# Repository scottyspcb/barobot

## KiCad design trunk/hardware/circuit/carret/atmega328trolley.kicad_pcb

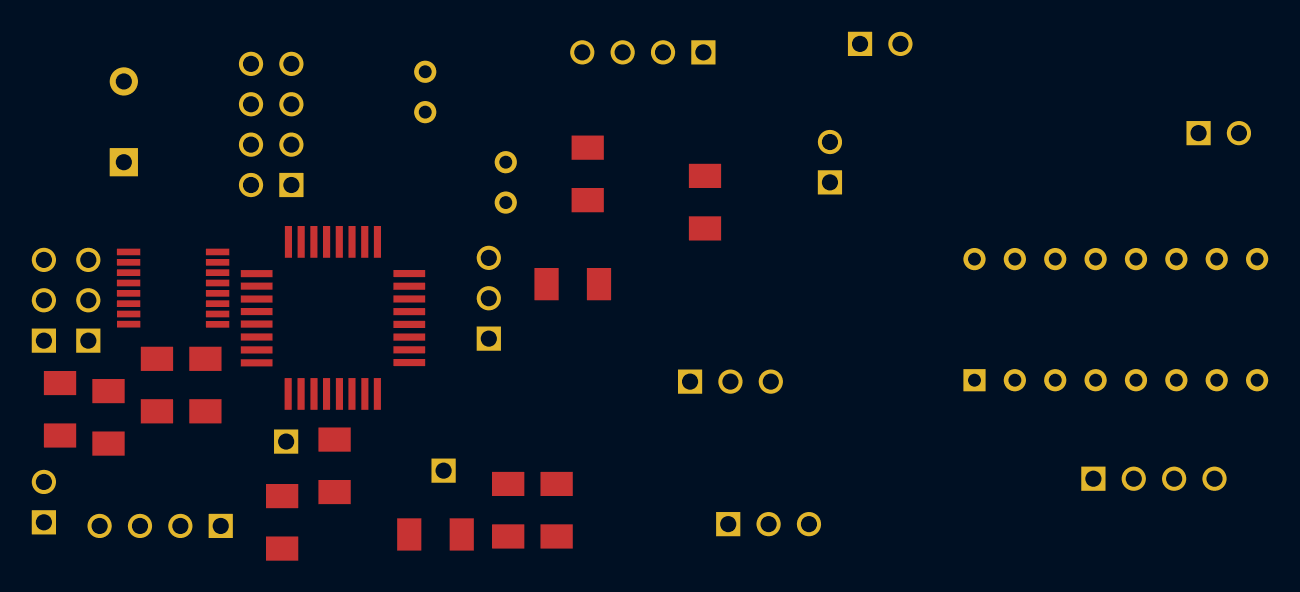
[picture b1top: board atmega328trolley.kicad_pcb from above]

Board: 2 copper layers, 33 parts (0 on the bottom side), 49 nets, no tracks yet.

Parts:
C1, C2: 27p; C1
C3, C4, C5: 100nF; SM1206
C6: 100uF; C2V10
IC1: ATMEGA328P-A; TQFP32
P1: CONN_10; pin_array_4x2
P2, P3: CONN_1; PIN_ARRAY_1
P4, P5, P8: CONN_4; PIN_ARRAY_4x1
P6, P7, P10: CONN_2; PIN_ARRAY_2X1
P9: DIL16; DIP-16__300
R1: 10k; SM1206
R3, R4, R5, R6, R7, R8, R9, R10: 330; SM1206
Servo_Y1: CONN_3; PIN_ARRAY_3X1
Servo_Z1: CONN_3; PIN_ARRAY_3X1
U1: ULN2803A; tssop-16
UART1: CONN_3; PIN_ARRAY_3X1
X1: 16MHz; PIN_ARRAY_2X1
hall_x1: CONN_3; PIN_ARRAY_3X1
hall_y1: CONN_3; PIN_ARRAY_3X1

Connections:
/PB0: IC1.12, U1.3
/PB1: IC1.13, U1.2
/PB2: IC1.14, U1.1
/PB3: IC1.15, P1.2
/PB4: IC1.16, P1.3
/PB5: IC1.17, P1.4
/PB6: C1.1, IC1.7, X1.2
/PB7: C2.1, IC1.8, X1.1
/PC0: IC1.23, hall_x1.1
/PC1: IC1.24, hall_y1.1
/PC2: IC1.25, P9.10, P9.11
/PC3: IC1.26, U1.8
/PC4: IC1.27, P1.5
/PC6: IC1.29, R1.1
/PD0: IC1.30, UART1.1
/PD1: IC1.31, UART1.2
/PD2: IC1.32, U1.5
/PD3: IC1.1, U1.6
/PD4: IC1.2, U1.7
/PD5: IC1.9, Servo_Z1.1
/PD6: IC1.10, Servo_Y1.1
/PD7: IC1.11, U1.4
/VCC: P1.6, P8.1, P9.1, P9.2, R1.2, hall_x1.3, hall_y1.3
/VCC6: P1.1, Servo_Y1.2, Servo_Z1.2
GND: C1.2, C2.2, C3.2, C4.2, C5.2, C6.2, IC1.3, IC1.5, IC1.21, P1.7, P1.8, P8.4, P9.3, P9.5, P9.12, Servo_Y1.3, Servo_Z1.3, U1.9, UART1.3, hall_x1.2, hall_y1.2
unnamed: P7.1, R3.1
unnamed: P4.3, P5.3, P6.2, P7.2
unnamed: P4.4, R7.1
unnamed: P4.2, R6.1
unnamed: IC1.22, P3.1
unnamed: IC1.19, P2.1
unnamed: P4.1, R5.1
unnamed: R7.2, U1.16
unnamed: P8.3, P9.7
unnamed: P9.4, P9.15
unnamed: P8.2, P9.6
unnamed: P9.9, P10.1
unnamed: P9.8, P10.2
unnamed: R8.2, U1.15
unnamed: R4.2, U1.11
unnamed: P6.1, R4.1
unnamed: R3.2, U1.12
unnamed: R10.2, U1.13
unnamed: R9.2, U1.14
unnamed: P5.4, R10.1
unnamed: C5.1, IC1.20
unnamed: P5.2, R9.1
unnamed: P5.1, R8.1
PWR: C3.1, C4.1, C6.1, IC1.4, IC1.6, IC1.18, U1.10

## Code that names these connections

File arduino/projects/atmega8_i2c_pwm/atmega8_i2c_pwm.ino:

#include <WSWire.h>
#include <i2c_helpers.h>

// ATMEL ATMEGA8 / ARDUINO
//
//                  +-\/-+
//            PC6  1|    |28  PC5 (A5/ D19)
//      (D0)  PD0  2|    |27  PC4 (A4/ D18)
//      (D1)  PD1  3|    |26  PC3 (A3/ D17)    L
//      (D2)  PD2  4|    |25  PC2 (A2/ D16)    L
//      (D3)  PD3  5|    |24  PC1 (A1/ D15)
//   L  (D4)  PD4  6|    |23  PC0 (A0/ D14)
//            VCC  7|    |22  GND
//            GND  8|    |21  AREF
//            PB6  9|    |20  AVCC
//            PB7 10|    |19  PB5 (D13)
//   L  (D5)  PD5 11|    |18  PB4 (D12)
//   L  (D6)  PD6 12|    |17  PB3 (D11) PWM
//   L  (D7)  PD7 13|    |16  PB2 (D10) PWM
//   L  (D8)  PB0 14|    |15  PB1 (D9) PWM      L
//                  +----+

// pin01  arduino --  PC6	RESET           - CONN1
// pin02  arduino 00  PD0	RX		- CONN2
// pin03  arduino 01  PD1	TX		- CONN2
// pin04  arduino 02  PD2	INT0		- SWITCH
// pin05  arduino 03  PD3	INT1		- CONN1
// pin06  arduino 04  PD4		        -
// pin07  arduino --  VCC
// pin08  arduino --  GND
// pin09  arduino ??  PB6	XTAL1		- 
// pin10  arduino ??  PB7	XTAL2		- 
// pin11  arduino 05  PD5                       - LED R TOP
// pin12  arduino 06  PD6                       - LED G TOP
// pin13  arduino 07  PD7                       - LED B TOP
// pin14  arduino 08  PB0                       - LED W TOP

// pin15  arduino 09  PB1			- 
// pin16  arduino 10  PB2	SS		- 
// pin17  arduino 11  PB3	MOSI		- CONN1
// pin18  arduino 12  PB4	MISO		- CONN1
// pin19  arduino 13  PB5	SCK		- CONN1
// pin20  arduino --  AVCC
// pin21  arduino --  AREF
// pin22  arduino --  GND
// pin23  arduino A0/D14  PC0	ADC0		- 
// pin24  arduino A1/D15  PC1	ADC1		- 
// pin25  arduino A2/D16  PC2	ADC2		- 
// pin26  arduino A3/D17  PC3	ADC3		- 
// pin27  arduino A4/D18  PC4	ADC4	SDA	- CONN1
// pin28  arduino A5/D19  PC5	ADC5	SCL	- CONN1

#define LEFT_RESET_PIN 14
#define MY_POKE_PIN 5

// to jest slave
#define VERSION 0x01
#define DEVICE_TYPE 0x10
#define MASTER_ADDR 0x01

volatile bool use_local = false;
volatile byte in_buffer1[5];

void setup(){
//  Serial.begin(38400);
//  Serial.begin(115200);
  if(!init_i2c()){
//    show_error(5 );
  }
//  pinMode(MY_POKE_PIN, INPUT);
  Wire.onReceive(receiveEvent);
  Wire.onRequest(requestEvent);
  send_here_i_am();  // wyslij ze oto jestem
}

long int mil = 0;
long int milis100 = 0;
boolean diddd = false;

void loop() {
  mil = millis();
  if( mil > milis100 + 4000 ){    // co 4 sek
        send_pin_value( MY_POKE_PIN, diddd ? 1 : 0 );
  milis100 = mil;
  }

    if( use_local&& in_buffer1[0] ){          // komendy bez odpowiedzi tutaj:
      byte command = in_buffer1[0];
      if( command == 0x11 ){                // PWM     3 bajty
           // setPWM(in_buffer1[1],in_buffer1[2]);
 //           leds[in_buffer1[1]].wypelnienie = in_buffer1[2];
      }else if( command == 0x10 ){          // reset
      }else if( command == 0x12 ){          // set time
      }else if( command == 0x13 ){          // fade
      }else if( command == 0x14 ){          // set dir
      }else if( command == 0x15 ){          // set output
      }else if( command == 0x16 ){          // Resetuj urządzenie obok
        pinMode(LEFT_RESET_PIN, OUTPUT); 
        digitalWrite(LEFT_RESET_PIN, LOW);  // pin w stanie niskim
      }else if( command == 0x17 ){          // Koniec resetu urządzenia obok, ustaw pin w stan wysokiej impedancji
        pinMode(LEFT_RESET_PIN, INPUT);     // set pin to input
        digitalWrite(LEFT_RESET_PIN, LOW);  // turn OFF pullup resistors
      }else if( command == 0x1E ){          // zmien address
      }
      in_buffer1[0] = 0;
      use_local = false;
   }
}

void receiveEvent(int howMany){
  byte cntr = 0;
  byte aa = 0;
  while( Wire.available()){ // loop through all but the last  
    aa = Wire.read(); // receive byte as a character
    in_buffer1[cntr] = aa;
    cntr++;
  }
  byte sss = (in_buffer1[0] >> 4);
  if ( sss == 1 ){      // najstarsze 8 bitów RÓWNE 1 to wykonaj w głównym wątku
      use_local = true;  
  }
}

void requestEvent(){ 
  // w in_buffer jest polecenie
    byte command = in_buffer1[0];
    if( command == 0x26 ){  // get analog value
    /*
        uint16_t value = analogRead(in_buffer1[1]);
        byte ttt[2]    = {value>>8, value & 0xff };
        Wire.write(ttt,2);*/
    }else if( command == 0x28 ){  // get digital value
      /*  boolean value  = digitalRead(in_buffer1[1]);
        byte ttt[1]    = {value ? 0xff:0xff};
        Wire.write(ttt,1);*/
    }else if( command == 0x29 ){          // TEPE + VERSION       3 bajty
        byte ttt[2] = {VERSION,DEVICE_TYPE};
        Wire.write(ttt,2);
    }else if( command == 0x2A ){    // return xor
        byte res = in_buffer1[1] ^ in_buffer1[2];
        Wire.write(res);
        if( res & 1 ){    // ustawiony najmlodzzy bit
//          diddd = !diddd;
//          digitalWrite(13, diddd);
        }
    }
}

static void send_pin_value( byte pin, byte value ){
  byte ttt[4] = {0x21,my_address,pin,value};
  send(ttt,4);
 // Serial.println("out "+ String( my_address ) +" / "+ String( pin ) +"/"+ String(value));
}
void send_poke(){
  byte ttt[2] = {0x22,my_address};
  send(ttt,2);
}
static void send_here_i_am(){
  byte ttt[2] = {0x23,my_address};
  send(ttt,2);
//  Serial.println("hello "+ String( my_address ));  
}
void send( byte buffer[], byte ss ){
  Wire.beginTransmission(MASTER_ADDR);  
  Wire.write(buffer,ss);
  byte error = Wire.endTransmission();
//  Serial.println("out "+ String( my_address ) +" / "+ String( pin ) +"/"+ String(value)+ "/e:" + String(error));
}


/*
void show_error( byte error_code ){    // mrygaj czerwonym tyle razy
  while(true){
    while(--error_code){
      digitalWrite(13, 1);
      delay2(100);    
      digitalWrite(13, 0);
      delay2(100);
    }
  }
}*/

/*
void serialEvent(){				       // FUNKCJA WBUDOWANA - zbieraj dane z serial0
	while (Serial.available()) {    // odczytuj gdy istnieja dane i poprzednie zostaly odczytane
		char inChar = (char)Serial.read(); 
                Serial.write(inChar);
	}
}*/

/*
void setPWM(byte pin, byte level){
    leds[pin].wypelnienie = level;
    Serial.println("setPWM:" + String(pin) + "/" + String(level) );
}
*/

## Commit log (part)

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2014-03-17 Hall detecting
2014-03-17 Added drink creator activity and updated color scheme and shit
2014-03-17 Splitet main app into libs
2014-03-17 Merged
2014-03-17 Added merged R.java
2014-03-17 Only one main Queue Send full X position
2014-03-18 New view: Manual bottle position change Negative position from arduino
2014-03-18 Added Pour functionality
2014-03-18 It works. Cheers!
2014-03-18 Some UI tweaks
2014-03-18 Missing files
2014-03-18 Added icons to main menu
2014-03-18 Updated menu bar
2014-03-19 Added new background and transparency
2014-03-19 Setting position from hall Changed margins for slots
2014-03-19 Updated Product Activity for transparency
2014-03-19 Further GUI tweaks and updates
2014-03-19 Changed database to persistent mode
2014-03-19 Design model
2014-03-19 Added shadows to text on product activity
2014-03-19 Added gen to ignore list
2014-03-19 Cleaned up a bit
2014-03-22 Intro to Upanel address detecting
2014-03-22 Extracted hardware state from android app
2014-03-22 Added files to ignored
2014-03-25 Added main color picker Repaider audio detedction
2014-03-25 Less warnings Upanels detecting Intro to real barobot ISP programmer Added drink carusel for tests
2014-03-26 Added dice image
2014-03-28 Upanel searching on android
2014-03-30 Refacotirisation
2014-04-02 auto detect leds
2014-04-02 Modified the look of main menu(including changing icons). Added Options screen.
2014-04-08 Updated create icon
2014-04-08 updated Choose icon
2014-04-08 Added Recipe Atrribute Bars and some changes to the IngredientListFragment
2014-04-09 Further changes to GUI
2014-04-09 - Made recipe properties work - added properties to liquids - changed main page layout - made "Try Favorite" work properly.
2014-04-09 Created wiki page through Technical details
2014-04-10 Added breadcrumbs to main menu
2014-04-10 Cosmetic changes
2014-04-13 Deleted unimportant files
2014-04-13 Added real foto
2014-04-13 Automatic upanel detection Deleted unimportant files
2014-04-13 Added adb_usb.ini for local adb tool Added inital drinks images
2014-04-13 Added compiled and released packages.
2014-04-16 Nie tworzenie nowej bazy za kazdym razem
2014-04-17 Changed drinks photos
2014-04-19 Added a batch of small fixes for GUI
2014-04-20 Added some more small fixes and drops on create screen
2014-04-21 Improved servo test
2014-04-21 New config for commands
2014-04-21 Added imlementation of Async Stepper driver
2014-04-21 Added arduino MCU definitions
2014-04-22 Repaired Tester project in Windows 8 64bit (serial port connection)
2014-04-22 Repaired paths for arduino libs
2014-04-30 Added new ilumination effect Fixed save settings bug in Android
2014-05-01 Added Disclaimer.txt
2014-05-06 Added new method for leds on upanels
2014-05-07 Extracted engine X driver to lib Added some ilumination schemas
2014-05-09 Repaired reseting when trying to pour from back bottles
2014-05-10 Screen Orientation to ladscape Demo mode stub
2014-05-13 Added drink images Changed i2c delays Remove recipe button
2014-05-16 Added partlist
2014-05-18 Edited wiki page TechnicalDetails through web user interface.
2014-05-21 Added BOM for USA
2014-05-21 Added graph of hall x
2014-05-21 Moved graph of hall x
2014-05-21 Implemented master LED power config
2014-05-21 Added architecture model
2014-05-21 Added BOM
2014-05-21 d 3d model in PDF
2014-05-28 Refactoring in web server Added UI for x margin
2014-05-28 Fixed dependencies Bigger bottles Added web assets
2014-05-28 Routes refactoring
2014-05-29 Changed "Pour" to "Start" Changed colors
2014-05-30 Refactoting virtualComponents Async driver Added dataobjects for Photo, Log and Positions
2014-05-30 Fixed upanel compilation error
2014-05-30 Using async stepper driver
2014-06-01 Fixed dead lock bug (synchronization error)
2014-06-01 Merged audio example do main
2014-06-02 Auto homing before drink Light show - detect minimum Config for max speed, repeat time
2014-06-05 Fixed synchronization bug
2014-06-07 Repaired homing Fixed bug with recipes setup Fixed synchronization
2014-06-23 Creader branch for non-upanel version
2014-06-23 Added neopixel lib
2014-06-23 Added non-upanel veriosn of firmware
2014-06-26 Added cheaper version of PCB
2014-06-29 Added new main view Merger serial lib
2014-06-29 Added l12n for drinks, liquids and types
2014-07-09 Changed main view
2014-07-28 Changes in stepper lib
2014-07-28 Changes in circuits
2014-07-28 Intro to magic led implementation Added lib for POST file upload Imporved coding style
2014-07-28 Added translation into PL and RU
2014-07-28 Intro to drinks synchronisation
2014-08-05 Repaired urls in www mode
2014-08-05 Intro to API
2014-08-05 Added remote controll
2014-08-06 Added magic led strip light theme
2014-08-06 Added default db
2014-08-06 Added serial lib
2014-08-15 Translations in RU
2014-08-16 Added new routes Ability to change dispenser capacity through UI
2014-08-17 Intro to ISP programming
2014-08-17 Changed circuits
2014-08-17 Added gerber files
2014-08-18 Added missing files
2014-08-19 Added JSON Api to SofaServer
2014-08-19 Added additional checks for do_drink page
2014-08-19 A wee bit fix of fatal error message formatting
2014-08-21 Added copy od released circuit
2014-08-22 Added a message to be displayed when we call a sofaserver do_drink page.
2014-08-25 Auto create database
2014-08-25 First version of API
2014-09-01 Added full screen mode
2014-09-01 Changed buttons collors Added full screen mode
2014-09-01 Deleted old files
2014-09-03 PCB THT resistors
2014-09-05 Added workaround for cross domain ajax call to API
2014-09-07 Added PDB with ina125
2014-09-08 Added test for servos
2014-09-12 Deleted unused project
2014-09-18 New version of pcbs
2014-09-19 New version of hardware (pcb tests)
2014-09-19 New version of upanels
2014-09-23 Added relase 3 PCB
2014-09-24 Added PCB realse 4
2014-09-24 Removed old files
2014-09-24 Fixed error with halls
2014-09-24 Added release 3 od pcb
2014-09-24 Added route for message debuging
2014-09-24 Added "commands" route
2014-09-28 New leds
2014-10-16 New leds Dont go up without magnet below Auto update firmware Arduino stats Update manager
2014-10-28 Deleted unused files
2014-10-28 Added error raporting (not required) Changed servo Z command Drink size in UI Refactorization of debug view Added Caibration Wizard Added
2014-11-06 Added calibration wizard Light manager refactorization
2014-11-20 Wizard Autoupdate
2014-11-20 Spelling
2014-11-24 Added settings activity
2014-11-27 Load cell
2014-12-03 Load cell and ansk for glass
2014-12-15 Added hall y wizard
2014-12-17 Auto update
2014-12-21 Version 10. Fixed Distillery missing problem. Fixed auto update problem Added hall Y calibration wizard
2014-12-21 Added latest revision of PCP
2014-12-21 Added latest revision of PCP (gerber files)
2014-12-30 Refactoring: hall Y, servo Y
2014-12-30 Refactoring: stepper X
2015-01-05 DEleted obsolete logic
2015-01-05 (Tests) Added code for RF radio
2015-01-06 Fixes in wizard Full screen issue
2015-01-07 Added drinkg photos
2015-01-07 Added new demo mode
2015-01-09 Fixed debugLeds, Added DOING_DRINK flag Added light demo preset
2015-01-11 RF24 radio tests
2015-01-11 Fixed homing bug Fixed "cant pour from the last bottle" bug
2015-01-18 New API methods Fixed in demo mode
2015-01-18 Introduced getOneObject() Optimized startup process - db usage
2015-01-18 Fixed problem with manual moving from "advanced settings"
2015-01-22 Added drink menu (on volume down button)
2015-01-22 Added colors test
2015-01-24 Fixed problem with calibration
2015-01-28 New PCB
2015-01-28 Added Log page to Sofa server
2015-02-08 Allow hide of lang bar
2015-02-09 Stop spilling when moving to back bottles. Added hall X tests
2015-02-10 Added 1.6 pcb
2015-02-13 Tests for new actuators
2015-02-16 Refactoring
2015-03-07 More tests
2015-03-18 New Web UI
2015-04-19 Barobot with actuators merge
2015-08-13 Migrating wiki contents from Google Code
